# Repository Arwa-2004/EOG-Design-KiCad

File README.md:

# EOG-Design-KiCad

## Table of Contents
1. [Introduction](#introduction)
2. [Components](#components)
   - [Protection Circuit](#protection-circuit)
   - [Boost Converter](#boost-converter)
   - [5V to -5V Inverting Converter](#5v-to--5v-inverting-converter)
   - [5V to 3.3V Regulator](#5v-to-33v-regulator)
   - [Li-ion Battery Charger](#li-ion-battery-charger)
   - [EOG Filters](#eog-filters)
   - [Flash Memory, UART, and Screen](#flash-memory-uart-and-screen)
   - [ESP32-WROOM-32E](#esp32-wroom-32e)
3. [PCB Design](#pcb-design)
4. [Future Work](#future-work)
5. [Copyright](#Copyright)

## Introduction
EOG (Electrooculography) is used in medical diagnostics to assess eye health and track issues related to the retina and cornea, it is handheld as electrodes are attached. The purpose of my project is to captures eye movement signals using EOG electrodes, processes the data with an ESP32 microcontroller, and displays the results on a screen.

## Components

### Protection Circuit
Is used to ensure that the system is safe from electrical surges. I used 2A fuse to protect against short circuits and overcurrent, a reverse polarity Schottky Diode, as its name suggests it protects the circuit from damage if the power supply is connected with reverse polarity, and a TVS diode SMAJ5.0A which protects sensitive components such as ESP32 from voltage spikes.

### Boost Converter
Which boosts the voltage from +3.6V to +5V, in this case I chose TPS61252DSG. The +5V rail is used to power the filters of EOG signal.

### 5V to -5V inverting converter
I used LM2776 to provide negative -5V supply to the EOG filters.

### 5V to 3.3V regulator 
Steps down the 5V supply to 3.3V for components like the ESP32, which require a 3.3V supply.

### Li-ion Battery Charger
Which charges a single-cell Li-ion battery (3.6V–4.2V) from a 5V input like USB or external adapter.
Charger IC LTC4001EUF#PBF manages the charging process, including constant current (CC) and constant voltage (CV) phases. Moreover, protects the battery from overcharging, over-discharging, and short circuits. Example of bettery used: https://tr.farnell.com/jauch/li18650jc-26-1s1p/batt-rechargeable-li-ion-2-6ah/dp/4551054

### EOG filters
As shown in the picture, I added a 3 pin connector for the electrodes (CH- and CH+) thrid one connected to ground which is behind the ear (in the bony area) as a reference https://store.upsidedownlabs.tech/product/bioamp-cable-v2/. I used instrumentation amplifier to amplify small differential signals from EOG electrodes while rejecting common-mode noise like interference from power lines 50Hz or 60Hz,or other sources.
The INA333xxDGK has a precise gain that can be set using a single external resistor, a high CMRR, and a low noise. 
I added user safety composed of TVS diodes to safeguard the user and the equipment from voltage spikes, electrostatic discharge (ESD), or reverse polarity.

Then, I connected IA to a high pass filter of 0.053Hz to process the amplified signal and remove unwanted DC low-frequency components, ensuring that only the relevant EOG signals (related to eye movements) are processed, which is connected to 50Hz notch filter to remove power line interference of 50Hz that is connected to class 1 and 2 of low pass filter, 1st class low pass filter 23.42Hz, is used to remove high-frequency noise and ensure that only the relevant EOG signals (typically in the range of 0.1 Hz to 30 Hz) are preserved. Furthermore, integrating 2nd class low-pass filter, 19.42Hz to effectively attenuates frequencies above the cutoff frequency (19.42 Hz), ensuring that high-frequency noise is removed more aggressively, which is conncted to the ESP32.

### Flash Memory, UART, and Screen
The OLED screen (AOM12864A0-1.54WW-ANO) to show EOG signals, eye movement patterns, or system parameters. The flash memory to store EOG signals for later analysis. Finally, UART to send EOG data to a computer for analysis. Note: this EOG is designed to retrieve or analyze the stored data later as needed as I'll depend on bluetooth build inside esp32 (coding) for data transfer. a BluetoothSerial used to communicate with a Bluetooth terminal app or custom software. In short I wont need a USB.

### ESP32-WROOM-32E
Is the brain of the system, since ESP32 enables communication between the EOG system and external devices,  processes the EOG signals captured by the electrodes and amplified/filtered by the analog front-end filters, displays real-time EOG data or system status on an OLED screen, and stores EOG data in flash memory or an external SD card for later analysis.

## PCB design
I used 4 layers (signal/ gnd/ power/ signal), I made sure that sensitive analog ciruits of the filters are far away from the noisy digital parts such as esp32, and I put decoupling capacitor 100 nF close to the power pins of each IC (ESP32, INA333xxDGK, filters, etc..)

## Future Work
This project is designed to retrieve and analyze stored EOG data as needed. Future improvements and planned features include:

1. **Bluetooth Data Transfer:**
   - The ESP32's built-in Bluetooth capability will be used for wireless data transfer, eliminating the need for a USB connection.
2. **Optimized Signal Processing:**
   - Further refinement of the EOG signal filters to improve noise immunity and signal accuracy.
   - Implementation of advanced signal processing algorithms (e.g., wavelet transforms) for better eye movement detection.

3. **Wireless Charging:**
   - Integration of a wireless charging module to enhance the portability and usability of the device.

4. **Mobile App Integration:**
   - Development of a mobile app to visualize EOG data in real-time and provide diagnostic insights.

## Copyright
Copyright (c) 2025 Arwa Basal
All rights reserved.

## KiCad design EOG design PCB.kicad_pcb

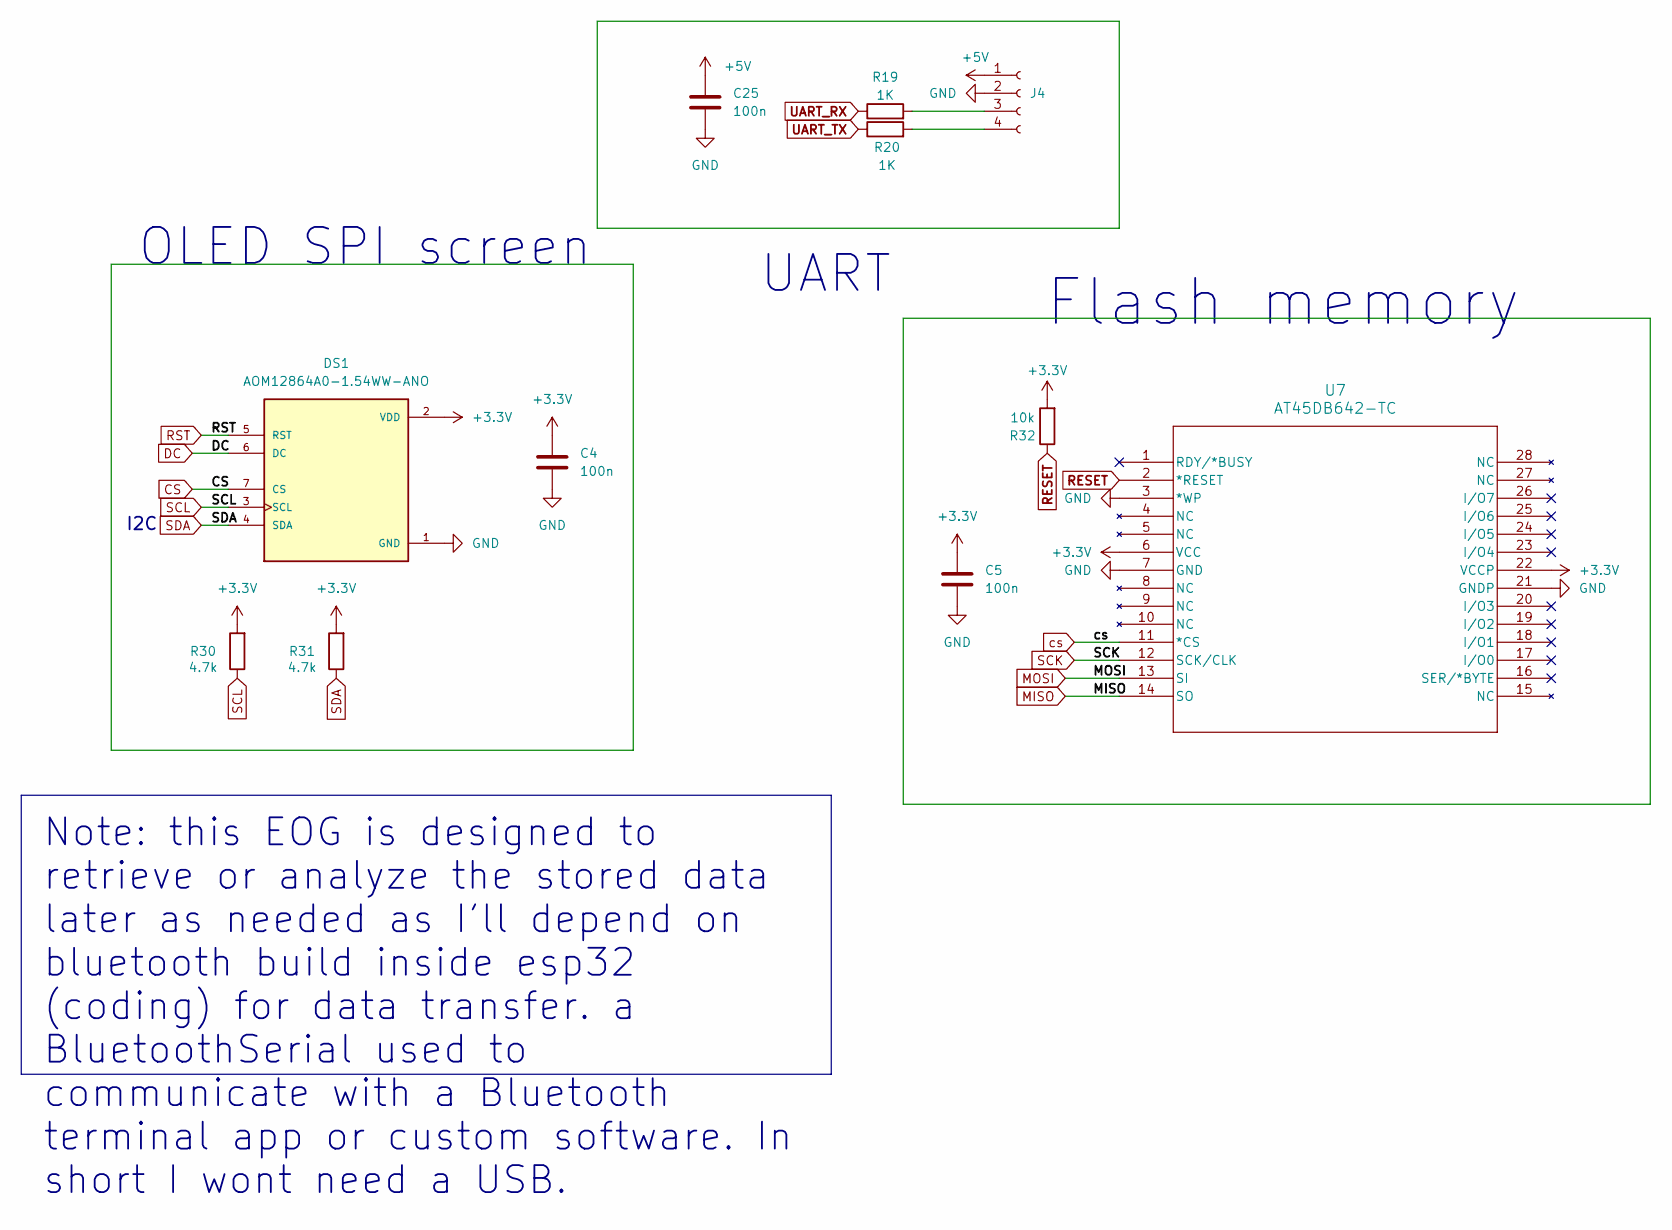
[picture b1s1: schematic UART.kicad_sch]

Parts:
C4, C5, C25: 100n; C_0603_1608Metric
DS1: AOM12864A0-1.54WW-ANO; LCD_AOM12864A0-1.54WW-ANO; PARTREV O; DigiKey_Part_Number 5491-AOM12864A0-1.54WW-ANO-ND
J4: Conn_01x04_Socket; PinHeader_2x02_P1.00mm_Vertical
R19, R20: 1K; R_0603_1608Metric
R30, R31: 4.7k; R_0603_1608Metric
R32: 10k; R_0603_1608Metric
U7: AT45DB642-TC; TSOP28_8x11P8_MCH

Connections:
+3.3V: C4.1, C5.1, DS1.2 (VDD), R30.2, R31.2, R32.2, U7.6 (VCC), U7.22 (VCCP); also elsewhere on the board
+5V: C25.1, J4.1; also elsewhere on the board
CS: DS1.7 (CS); also elsewhere on the board
DC: DS1.6 (DC); also elsewhere on the board
GND: C4.2, C5.2, C25.2, DS1.1 (GND), J4.2, U7.3 (*WP), U7.7 (GND), U7.21 (GNDP); also elsewhere on the board
MISO: U7.14 (SO); also elsewhere on the board
MOSI: U7.13 (SI); also elsewhere on the board
unnamed: J4.3, R19.2
unnamed: J4.4, R20.2
RESET: R32.1, U7.2 (*RESET)
RST: DS1.5 (RST); also elsewhere on the board
SCK: U7.12 (SCK/CLK); also elsewhere on the board
SCL: DS1.3 (SCL), R30.1; also elsewhere on the board
SDA: DS1.4 (SDA), R31.1; also elsewhere on the board
UART_RX: R19.1; also elsewhere on the board
UART_TX: R20.1; also elsewhere on the board
cs: U7.11 (*CS); also elsewhere on the board

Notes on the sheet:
Note: this EOG is designed to retrieve or analyze the stored data later as needed as I'll depend on bluetooth build inside esp32 (coding) for data transfer. a BluetoothSerial used to communicate with a Bluetooth terminal app or custom software. In short I wont need a USB.
OLED SPI screen
I2C
UART
Flash memory

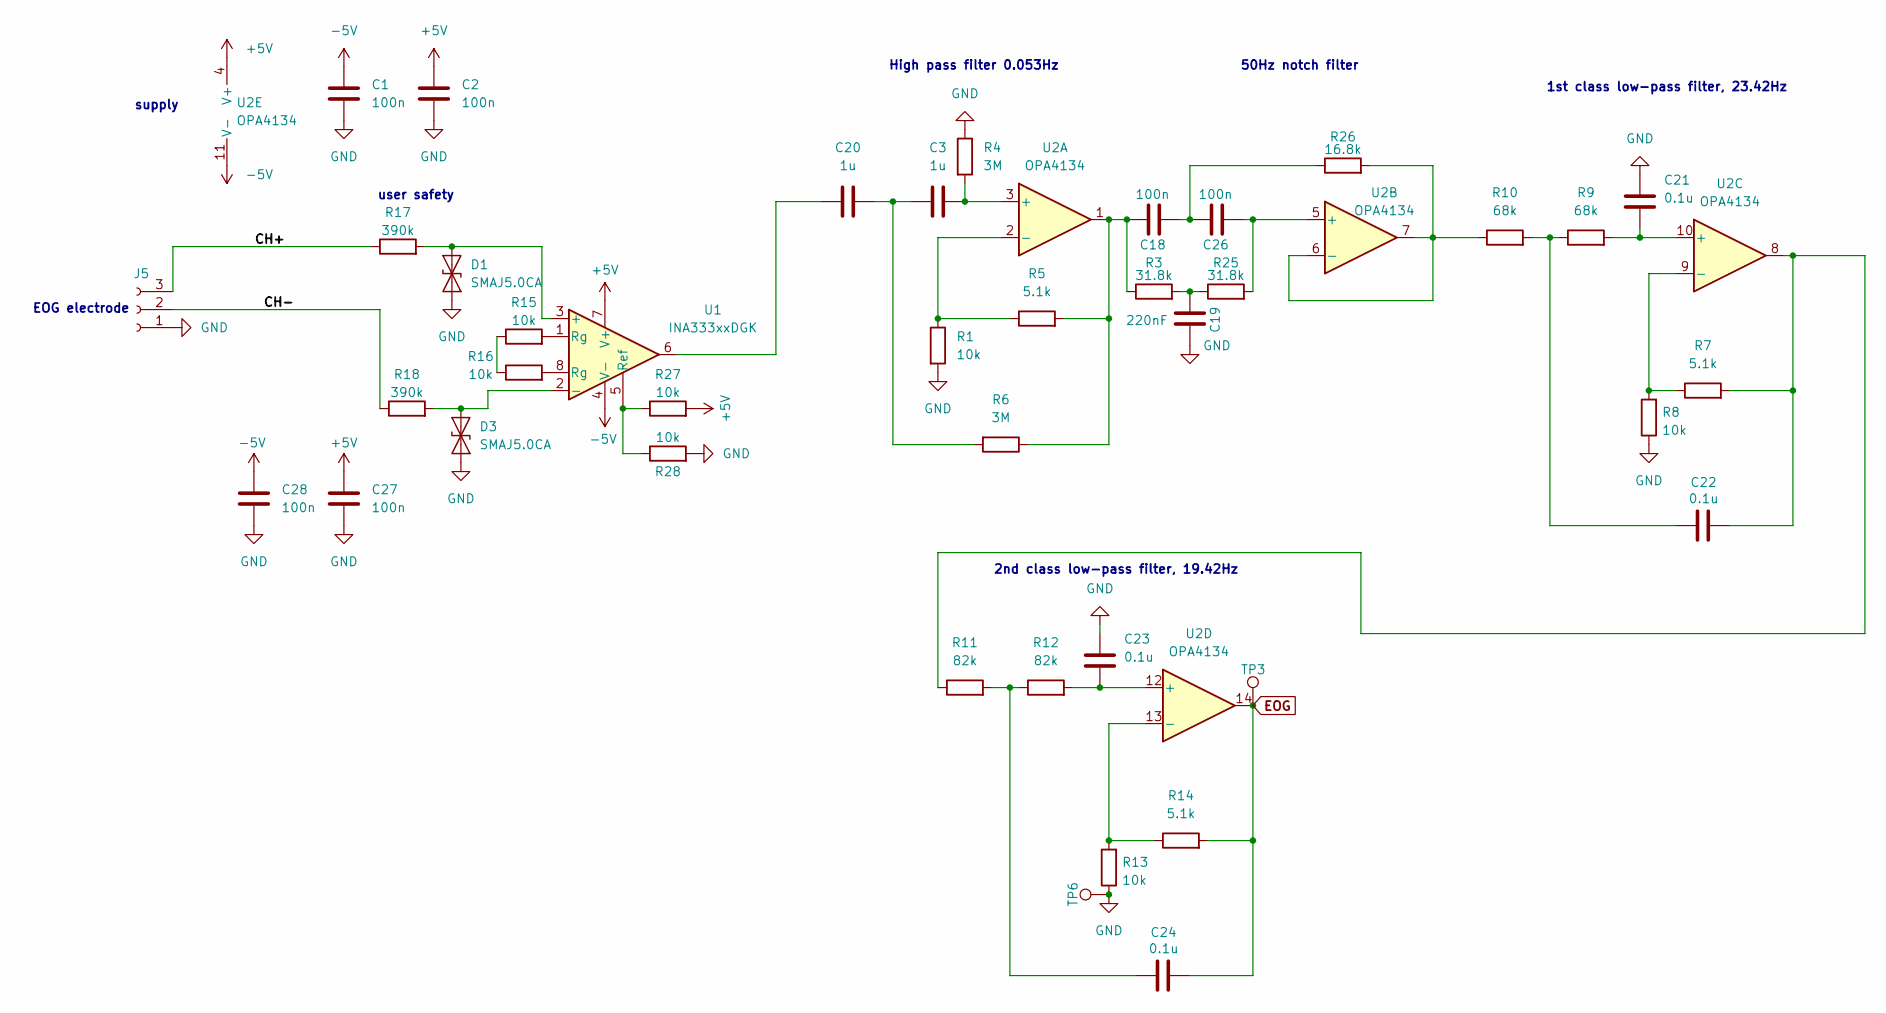
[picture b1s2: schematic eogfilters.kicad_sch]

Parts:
C1, C2, C18, C26, C27, C28: 100n; C_0603_1608Metric
C3, C20: 1u; C_0603_1608Metric
C19: 220nF; C_0603_1608Metric
C21, C22, C23, C24: 0.1u; C_0603_1608Metric
D1, D3: SMAJ5.0CA; D_SMA
J5: Conn_01x03_Socket; JST_PH_B3B-PH-K_1x03_P2.00mm_Vertical
R1, R8, R13, R15, R16, R27, R28: 10k; R_0603_1608Metric
R3, R25: 31.8k; R_0603_1608Metric
R4, R6: 3M; R_0603_1608Metric
R5: 5.1k; C_0805_2012Metric
R7, R14: 5.1k; R_0805_2012Metric
R9, R10: 68k; R_0603_1608Metric
R11, R12: 82k; R_0603_1608Metric
R17, R18: 390k; R_0603_1608Metric
R26: 16.8k; RES_SMR3DZ_VIS
TP3, TP6: TestPoint; TestPoint_Pad_D1.5mm
U1: INA333xxDGK; VSSOP-8_3x3mm_P0.65mm
U2: OPA4134; SOIC127P600X175-14N

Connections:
+5V: C2.1, C27.1, R27.2, U1.7 (V+), U2.4 (V+); also elsewhere on the board
-5V: C1.1, C28.1, U1.4 (V-), U2.11 (V-); also elsewhere on the board
/Filters/CH+: J5.3, R17.1
/Filters/CH-: J5.2, R18.1
EOG: C24.1, R14.2, TP3.1, U2.14; also elsewhere on the board
GND: C1.2, C2.2, C19.1, C21.2, C23.2, C27.2, C28.2, D1.1 (A1), D3.1 (A1), J5.1, R1.2, R4.1, R8.1, R13.1, R28.2, TP6.1; also elsewhere on the board
unnamed: C18.1, R3.1, R5.2, R6.1, U2.1
unnamed: C18.2, C26.1, R26.1
unnamed: C19.2, R3.2, R25.1
unnamed: C20.1, U1.6
unnamed: C3.1, C20.2, R6.2
unnamed: C22.1, R7.2, R11.1, U2.8
unnamed: C22.2, R9.1, R10.2
unnamed: C24.2, R11.2, R12.1
unnamed: D1.2 (A2), R17.2, U1.3 (+)
unnamed: D3.2 (A2), R18.2, U1.2 (-)
unnamed: R15.1, R16.1
unnamed: R15.2, U1.1 (Rg)
unnamed: R16.2, U1.8 (Rg)
unnamed: R27.1, R28.1, U1.5 (Ref)
unnamed: C3.2, R4.2, U2.3 (+)
unnamed: R1.1, R5.1, U2.2 (-)
unnamed: C26.2, R25.2, U2.5 (+)
unnamed: R10.1, R26.2, U2.6 (-), U2.7
unnamed: C21.1, R9.2, U2.10 (+)
unnamed: R7.1, R8.2, U2.9 (-)
unnamed: C23.1, R12.2, U2.12 (+)
unnamed: R13.2, R14.1, U2.13 (-)

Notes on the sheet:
supply
2nd class low-pass filter, 19.42Hz
50Hz notch filter
user safety
High pass filter 0.053Hz
EOG electrode
1st class low-pass filter, 23.42Hz

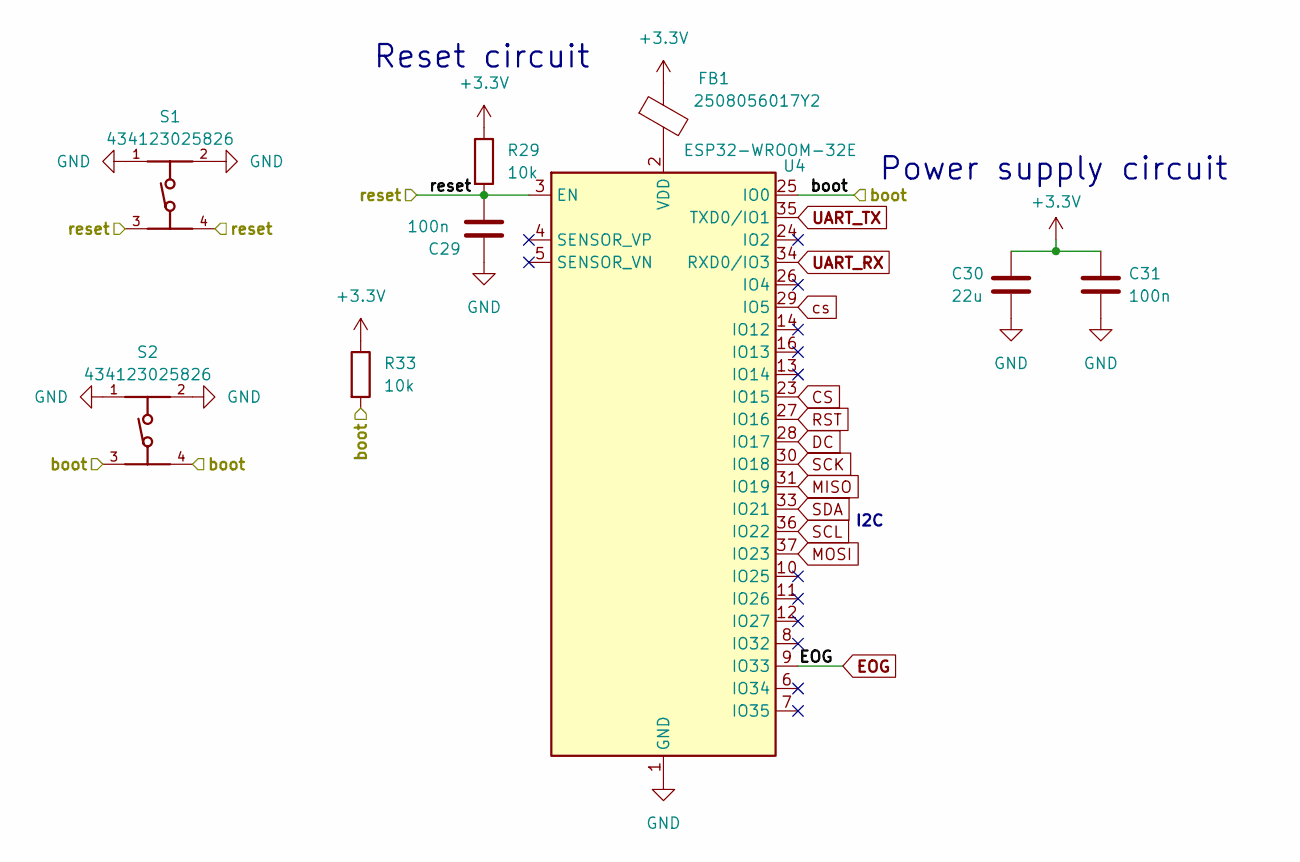
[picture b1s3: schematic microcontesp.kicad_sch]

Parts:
C29, C31: 100n; C_0603_1608Metric
C30: 22u; C_0805_2012Metric
FB1: 2508056017Y2; IND_25_0805_FRT
R29, R33: 10k; R_0603_1608Metric
S1, S2: 434123025826; PART-NUMBER 434123025826
U4: ESP32-WROOM-32E; ESP32-WROOM-32D

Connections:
+3.3V: C30.1, C31.1, FB1.1, R29.1, R33.1; also elsewhere on the board
/ESP32-WROOM-32E/boot: R33.2, S2.3, S2.4, U4.25 (IO0)
/ESP32-WROOM-32E/reset: C29.2, R29.2, S1.3, S1.4, U4.3 (EN)
CS: U4.23 (IO15); also elsewhere on the board
DC: U4.28 (IO17); also elsewhere on the board
EOG: U4.9 (IO33); also elsewhere on the board
GND: C29.1, C30.2, C31.2, S1.1, S1.2, S2.1, S2.2, U4.1 (GND), U4.15 (GND), U4.38 (GND), U4.39 (GND); also elsewhere on the board
MISO: U4.31 (IO19); also elsewhere on the board
MOSI: U4.37 (IO23); also elsewhere on the board
unnamed: FB1.2, U4.2 (VDD)
RST: U4.27 (IO16); also elsewhere on the board
SCK: U4.30 (IO18); also elsewhere on the board
SCL: U4.36 (IO22); also elsewhere on the board
SDA: U4.33 (IO21); also elsewhere on the board
UART_RX: U4.34 (RXD0/IO3); also elsewhere on the board
UART_TX: U4.35 (TXD0/IO1); also elsewhere on the board
cs: U4.29 (IO5); also elsewhere on the board

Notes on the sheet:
Reset circuit
Power supply circuit
I2C

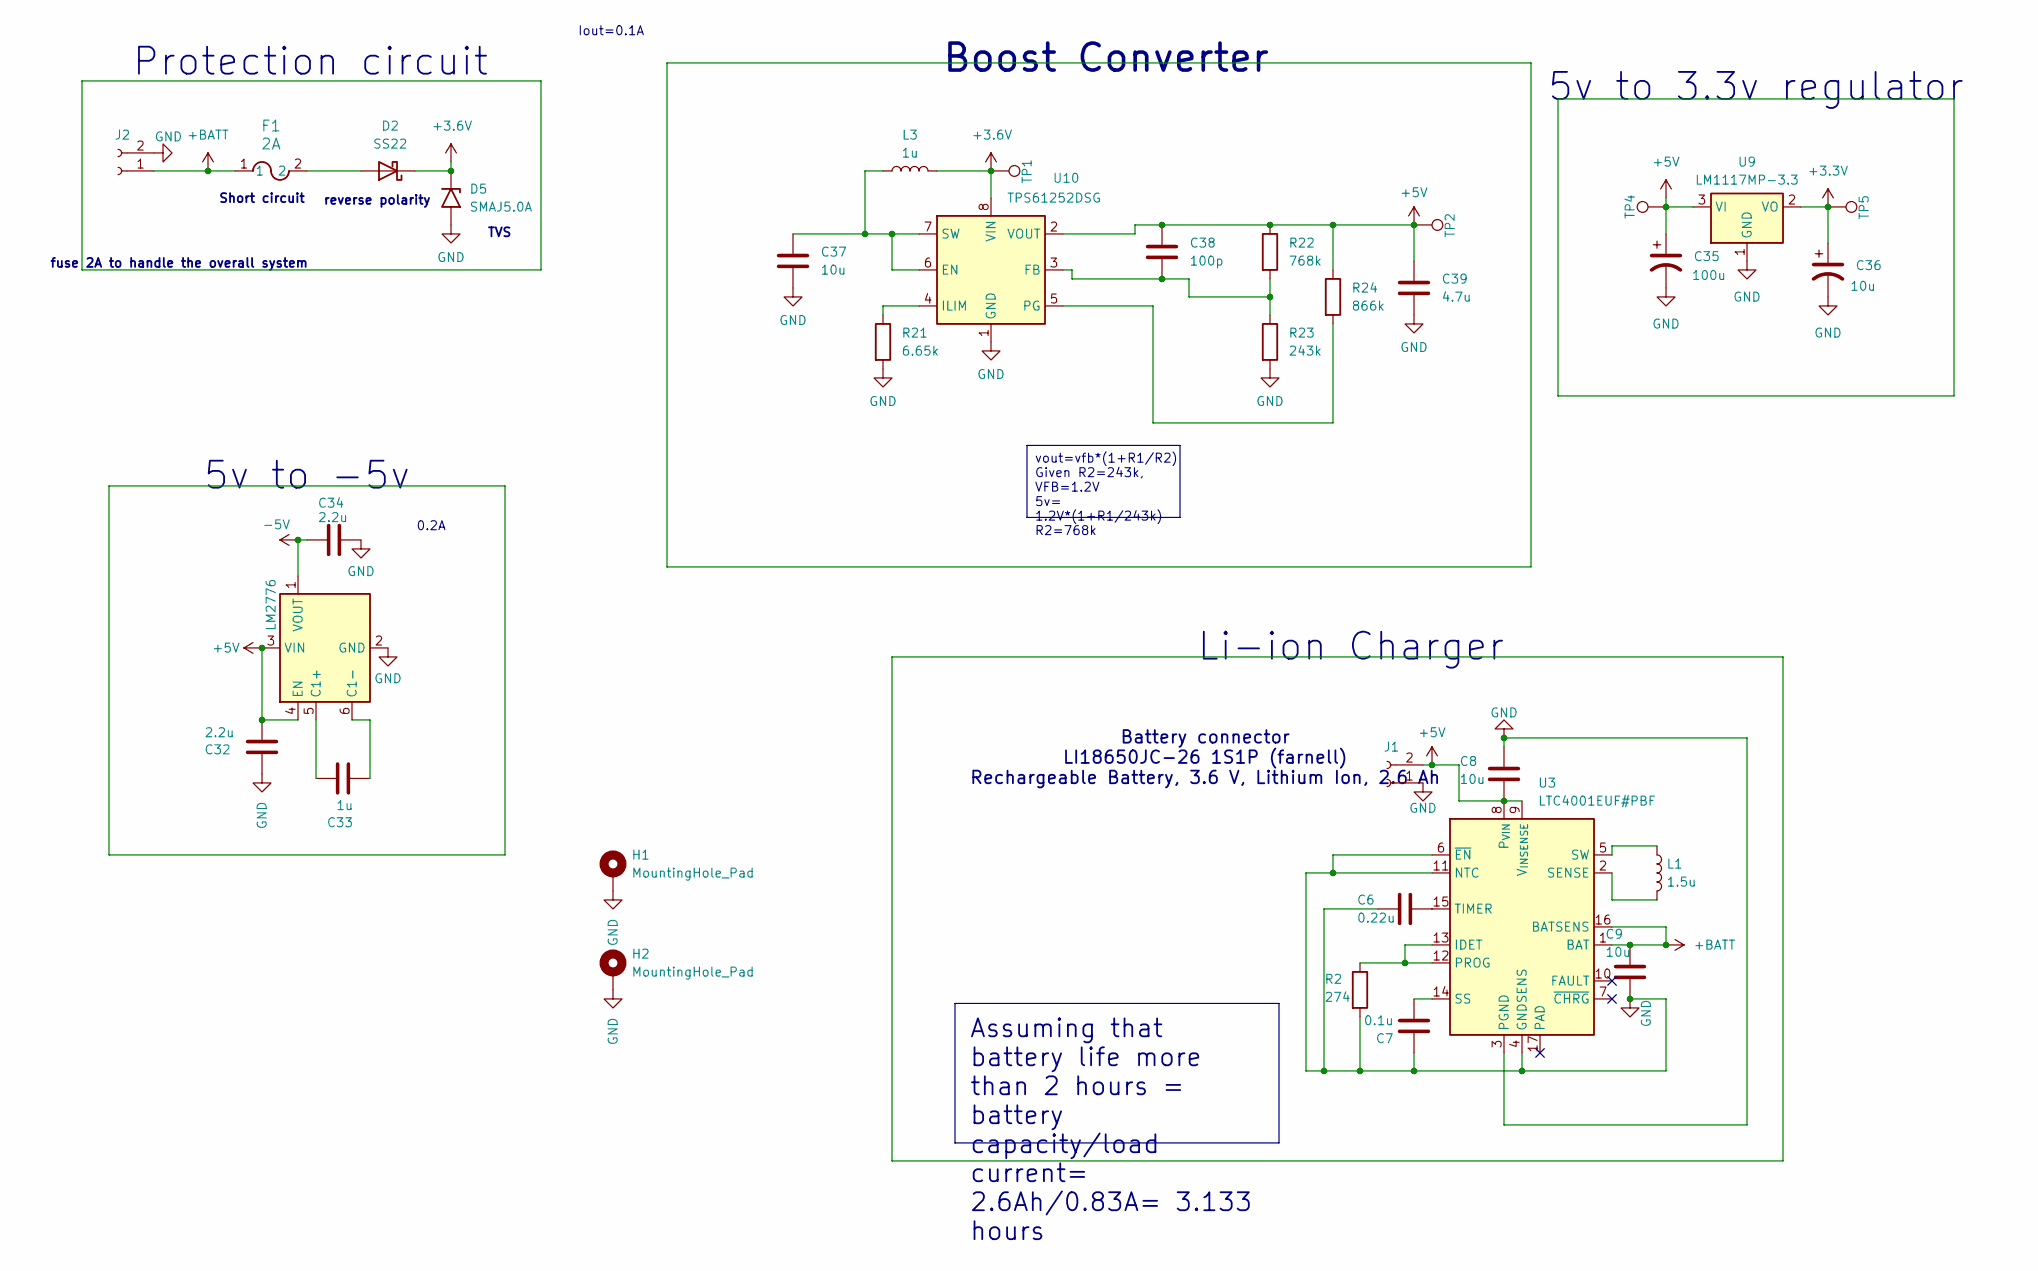
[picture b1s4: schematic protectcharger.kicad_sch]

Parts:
C6: 0.22u; C_0603_1608Metric
C7: 0.1u; C_0603_1608Metric
C8, C9: 10u; C_0805_2012Metric
C32, C34: 2.2u; C_0603_1608Metric
C33: 1u; C_0603_1608Metric
C35: 100u; WCAP-ATG8_5X11_DXL_
C36: 10u; WCAP-ATG8_5X11_DXL_
C37: 10u; C_0603_1608Metric
C38: 100p; C_0603_1608Metric
C39: 4.7u; C_0402_1005Metric
D2: SS22; D_SMA
D5: SMAJ5.0A; D_SMA
F1: 2A; Fuse_0603_1608Metric
H1, H2: MountingHole_Pad; MountingHole_3.2mm_M3_Pad
J1: LI18650JC-26 1S1P (farnell); JST_XA_B02B-XASK-1_1x02_P2.50mm_Vertical
J2: Conn_01x02_Socket; JST_XA_B02B-XASK-1_1x02_P2.50mm_Vertical
L1: 1.5u; INDC2016X100N
L3: 1u; INDC2016X100N
R2: 274; R_0805_2012Metric
R21: 6.65k; R_0402_1005Metric
R22: 768k; R_0402_1005Metric
R23: 243k; R_0402_1005Metric
R24: 866k; R_0201_0603Metric
TP1, TP2, TP4, TP5: TestPoint; TestPoint_Pad_D1.5mm
U3: LTC4001EUF#PBF; QFN-16-1EP_4x4mm_P0.65mm_EP2.15x2.15mm
U8: LM2776; SOT-23-6
U9: LM1117MP-3.3; SOT-223-3_TabPin2
U10: TPS61252DSG; WSON-8-1EP_2x2mm_P0.5mm_EP0.9x1.6mm

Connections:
+3.3V: C36.1, TP5.1, U9.2 (VO); also elsewhere on the board
+3.6V: D2.1 (K), D5.1 (A1), L3.2, TP1.1, U10.8 (VIN)
+5V: C8.2, C32.2, C35.1, C38.1, C39.1, J1.2, R22.1, R24.1, TP2.1, TP4.1, U3.8 (P_{VIN}), U3.9 (V_{INSENSE}), U8.3 (VIN), U8.4 (EN), U9.3 (VI), U10.2 (VOUT); also elsewhere on the board
+BATT: C9.1, F1.1, J2.1, U3.1 (BAT), U3.16 (BATSENS)
-5V: C34.1, U8.1 (VOUT); also elsewhere on the board
GND: C6.2, C7.1, C8.1, C9.2, C32.1, C34.2, C35.2, C36.2, C37.2, C39.2, D5.2 (A2), H1.1, H2.1, J1.1, J2.2, R2.2, R21.2, R23.2, U3.3 (PGND), U3.4 (GNDSENS), U3.6 (~EN), U3.11 (NTC), U8.2 (GND), U9.1 (GND), U10.1 (GND), U10.9 (GND); also elsewhere on the board
unnamed: D2.2 (A), F1.2
unnamed: R2.1, U3.12 (PROG), U3.13 (IDET)
unnamed: L1.2, U3.2 (SENSE)
unnamed: C7.2, U3.14 (SS)
unnamed: L1.1, U3.5 (SW)
unnamed: C6.1, U3.15 (TIMER)
unnamed: C33.1, U8.5 (C1+)
unnamed: C33.2, U8.6 (C1-)
unnamed: C37.1, L3.1, U10.6 (EN), U10.7 (SW)
unnamed: C38.2, R22.2, R23.1, U10.3 (FB)
unnamed: R21.1, U10.4 (ILIM)
unnamed: R24.2, U10.5 (PG)

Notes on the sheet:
vout=vfb*(1+R1/R2) Given R2=243k, VFB=1.2V 5v= 1.2V*(1+R1/243k) R2=768k
Assuming that battery life more than 2 hours = battery capacity/load current= 2.6Ah/0.83A= 3.133 hours
5v to -5v
reverse polarity
Short circuit
Iout=0.1A
0.2A
fuse 2A to handle the overall system
Protection circuit
Boost Converter
Battery connector LI18650JC-26 1S1P (farnell) Rechargeable Battery, 3.6 V, Lithium Ion, 2.6 Ah
Li-ion Charger
5v to 3.3v regulator
TVS

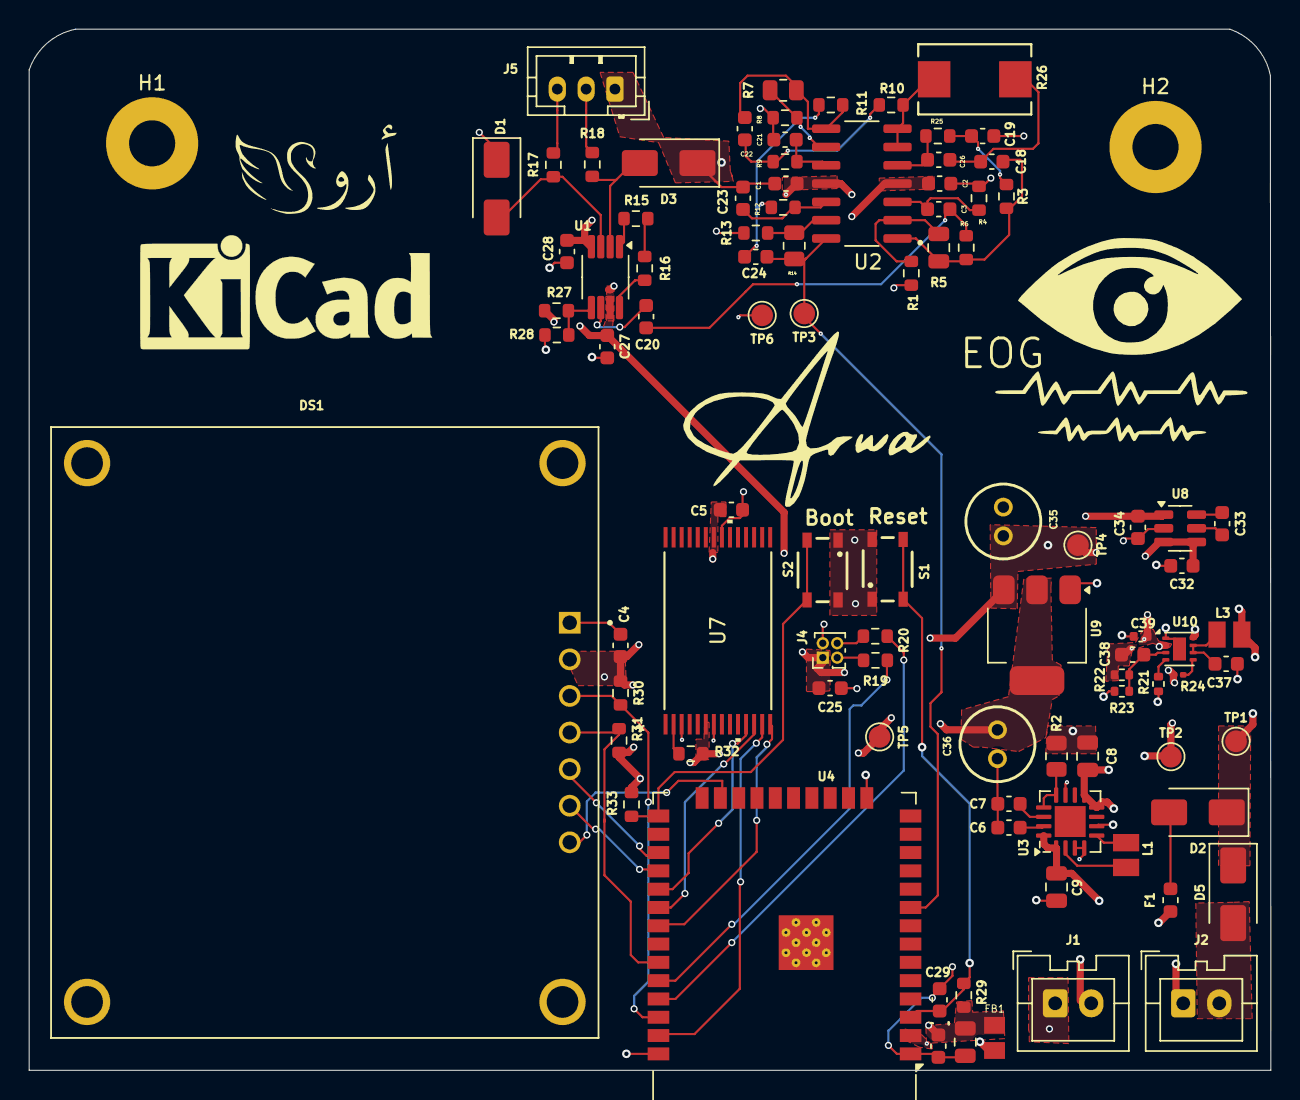
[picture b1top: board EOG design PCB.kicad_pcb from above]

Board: 4 copper layers, 86.2 x 72.3 mm, 95 parts (0 on the bottom side), 60 nets.

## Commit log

2025-02-04 Create COPYRIGHT
